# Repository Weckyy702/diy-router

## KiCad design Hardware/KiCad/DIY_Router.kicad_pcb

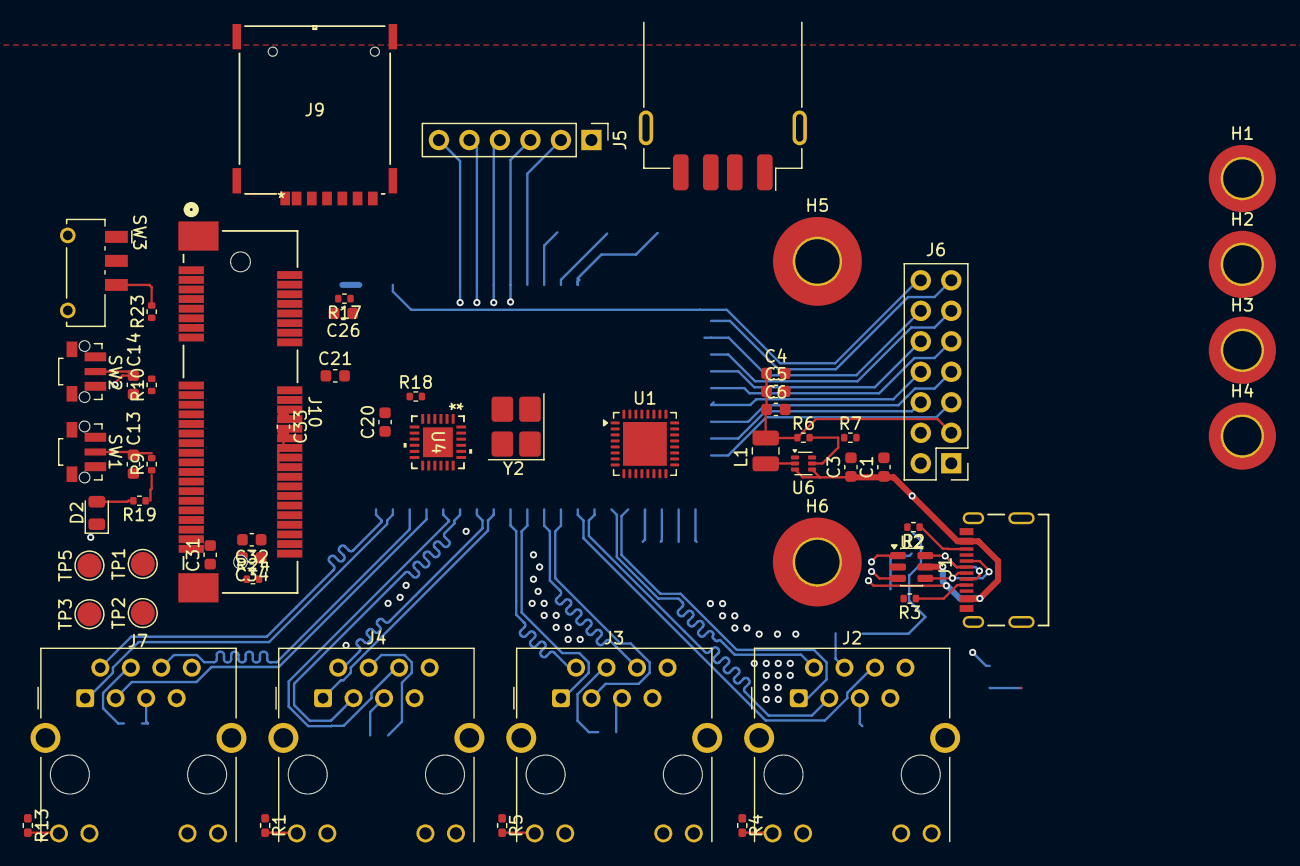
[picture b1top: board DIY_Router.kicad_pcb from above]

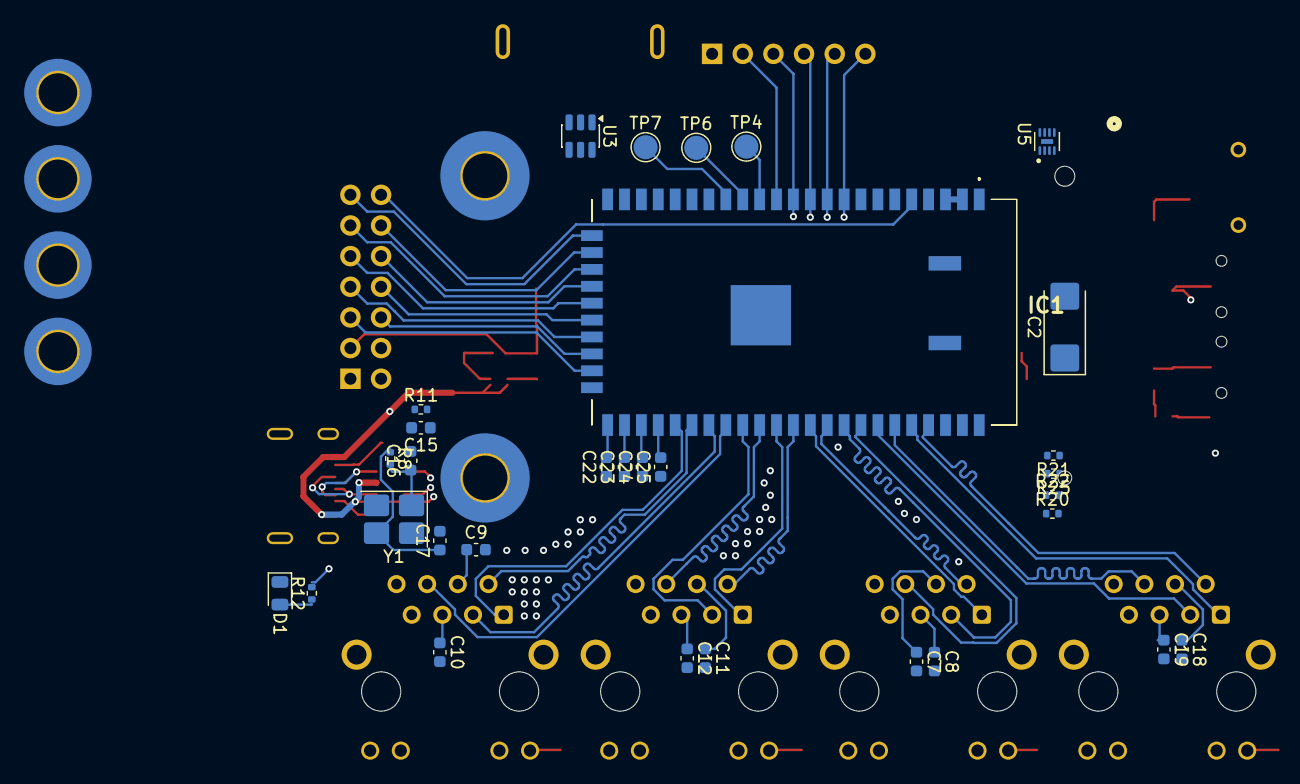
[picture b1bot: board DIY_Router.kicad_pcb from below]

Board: 4 copper layers, 90 parts (31 on the bottom side), 101 nets.

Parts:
C1, C3, C4, C5, C6: 22μF; C_0603_1608Metric
C2: 470µF; CP_EIA-6032-28_Kemet-C_HandSolder
C7, C8, C9, C10, C11, C12, C13, C14, C18, C19, C22, C23, C24, C25, C26, C31, C33: 100nF; C_0603_1608Metric
C15: 4.7µF; C_0603_1608Metric
C16, C17, C20, C21: 18pF; C_0603_1608Metric
C32: 1pF; C_0603_1608Metric
C34: 1µF; C_0603_1608Metric
D1, D2: LED; LED_0805_2012Metric
H1, H2, H3, H4: MountingHole_Pad; MountingHole_3.2mm_M3_DIN965_Pad_TopBottom
H5, H6: MountingHole_Pad; MountingHole_3.7mm_Pad_TopBottom
IC1: HLK-7628N; HLK7628N
J1: 2171790001; MOLEX_2171790001
J2, J3, J4, J7: RJ45_Hanrun_HR911105A_Horizontal
J5: Conn_01x06_Pin; PinHeader_1x06_P2.54mm_Vertical
J6: Conn_02x07_Odd_Even; PinHeader_2x07_P2.54mm_Vertical
J8: USB_A; USB_A_Receptacle_GCT_USB1046
J9: SIM8066-6-1-14-01-A; CONN_SIM8066-6-1-14-01-A_GCT
J10: 2041262-1; CONN60_2041262-1_TEC
L1: MGV252010R22M-10; L_1008_2520Metric
R1, R4, R5, R13: 1kR; R_0402_1005Metric_Pad0.72x0.64mm_HandSolder
R2, R3: 5.1kR; R_0402_1005Metric
R6: 453kR; R_0402_1005Metric
R7, R24, R25: 100kR; R_0402_1005Metric
R8: 1MR; R_0402_1005Metric
R9, R10, R23: 10kR; R_0402_1005Metric
R11: 226R 1%; R_0402_1005Metric
R12, R19: 220R; R_0402_1005Metric
R17: 15kR; R_0402_1005Metric
R18: 12kR 1%; R_0402_1005Metric
R20, R21, R22: 50kR; R_0402_1005Metric
SW1, SW2: 436333033816; SW_Wurth_WS-TASU_436333033816
SW3: 450405020524; SW_Wurth_WS-SLSU_450405020524
TP1, TP2, TP3, TP4, TP5, TP6, TP7: TestPoint; TestPoint_Pad_D2.0mm
U1: XR22801IL32TR-F; QFN-32-1EP_5x5mm_P0.5mm_EP3.65x3.65mm
U2, U3: USBLC6-2SC6Y; SOT-23-6
U4: USB2422T/MJ; SQFN24_4X4MC_MCH
U5: EMIF03-SIM02M8; SON40P170X150X60-9N
U6: TPS62A06ADRLR; SOT-563
Y1: ABM8-25.000MHZ-B2-T3; Crystal_SMD_3225-4Pin_3.2x2.5mm_HandSoldering
Y2: ABM8-24.000MHZ-B2-T; Crystal_SMD_3225-4Pin_3.2x2.5mm_HandSoldering

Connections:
+3.3V: C2.1, C4.1, C5.1, C6.1, C31.2, C33.1, C34.1, IC1.2 (3.3VD_1), IC1.3 (3.3VD_2), J6.3, J10.2, J10.39, J10.41, J10.52, L1.2, R1.1, R4.1, R5.1, R6.1, R9.1, R10.1, R13.1, R19.1, R21.2, U4.18 (VDD33)
/DIY_Router/GPIO0: IC1.30 (GPIO0), J6.7
/DIY_Router/I2C_SCL: IC1.24 (I2C_SCLK), J6.13
/DIY_Router/I2C_SDA: IC1.25 (I2C_SD), J6.12
/DIY_Router/SPI_CLK: IC1.27 (SPI_CLK), J6.10
/DIY_Router/SPI_CS0: IC1.5 (SPI_CS0), J6.14
/DIY_Router/SPI_CS1: IC1.26 (SPI_CS1), J6.11
/DIY_Router/SPI_MISO: IC1.28 (SPI_MISO), J6.9
/DIY_Router/SPI_MOSI: IC1.29 (SPI_MOSI), J6.8
/Mini_PCIe_SIM/LED_WWAN: D2.1 (K), J10.42
/Mini_PCIe_SIM/USIM_CLK: J10.12, U5.3 (CLKIN)
/Mini_PCIe_SIM/USIM_DATA: J10.10, U5.4 (DATAIN)
/Mini_PCIe_SIM/USIM_RST: J10.14, U5.2 (RSTIN)
/Mini_PCIe_SIM/W_DISABLE: J10.20, R23.1, TP2.1 (1_1)
/USB_Ethernet_UART_Bridge/CAP: C15.1, U1.3 (CAP1), U1.20 (CAP2)
/USB_Ethernet_UART_Bridge/XTALIN: C17.1, R8.1, U1.10 (XTALIN), Y1.3
/USB_Ethernet_UART_Bridge/XTALOUT: C16.1, R8.2, U1.9 (XTALOUT), Y1.1
/USB_HUB/USB_OUT_DN: U3.4 (I/O2), U4.2 (USBDM_DN1*PART_DIS_M1)
/USB_HUB/USB_OUT_DP: U3.6 (I/O1), U4.3 (USBDP_DN1*PART_DIS_P1)
/USB_HUB/XTALIN: C21.1, U4.22 (XTALIN*CLKIN), Y2.3
/USB_HUB/XTALOUT: C20.1, U4.21 (XTAOUT*(CLKIN_EM)), Y2.1
CPU_RST: C13.1, IC1.14 (PORST_N), R9.2, SW1.2, TP4.1 (1_1)
EPHY_LED0: IC1.13 (EPHY_LED0), J5.2
EPHY_LED1: IC1.12 (EPHY_LED1), J2.10, J5.3
EPHY_LED2: IC1.11 (EPHY_LED2), J3.10, J5.4
EPHY_LED3: IC1.10 (EPHY_LED3), J4.10, J5.5
EPHY_LED4: IC1.9 (EPHY_LED4), J5.6, J7.10
ETH_RX+: C24.1, U1.15 (ETH_RX+)
ETH_RX-: C25.1, U1.16 (ETH_RX-)
ETH_TX+: C22.1, U1.14 (ETH_TX+)
ETH_TX-: C23.1, U1.13 (ETH_TX-)
GND: C1.2, C2.2, C3.2, C4.2, C5.2, C6.2, C7.2, C8.2, C9.2, C10.2, C11.2, C12.2, C13.2, C14.2, C15.2, C16.2, C17.2, C18.2, C19.2, C20.2, C21.2, C26.1, C31.1, C32.1, D1.1 (K), H1.1 (1_1), H2.1 (1_1), H3.1 (1_1), H4.1 (1_1), H5.1 (1_1), H6.1 (1_1), IC1.1 (GND_1), IC1.4 (GND_2), IC1.21 (GND_3), IC1.23 (GND_4), IC1.56 (GND_5), IC1.EP1, IC1.EP2, IC1.EP3, J1.A1B12 (GND1), J1.B1A12 (GND2), J1.SH1 (SHIELD1), J1.SH2 (SHIELD2), J1.SH3 (SHIELD3), J1.SH4 (SHIELD4), J2.8, J2.SH, J3.8, J3.SH, J4.8, J4.SH, J5.1, J6.1, J6.2, J7.8, J7.SH, J8.4 (GND), J8.SH (Shield), J9.C5 (GND), J9.GND1, J9.GND2, J9.GND3, J9.GND4, J10.4, J10.9, J10.15, J10.18, J10.21, J10.26, J10.27, J10.29, J10.34, J10.35, J10.37, J10.40, J10.43, J10.50, R2.2, R3.2, R7.2, R11.1, R18.2, R20.2, R22.2, R25.1, SW1.1 (A), SW1.3, SW2.1 (A), SW2.3, SW3.2, U1.4 (GND), U1.12 (GND), U1.21 (GND), U1.22 (GND), U1.28 (GND), U1.33 (EPAD), U2.2 (GND), U3.2 (GND), U4.25 (EPAD), U5.9 (GND), U6.1 (GND), Y1.2 (G), Y1.4 (G), Y2.2 (G), Y2.4 (G)
MDI_P0_RN: C23.2, IC1.35 (MDI_RN_P0)
MDI_P0_RP: C22.2, IC1.34 (MDI_RP_P0)
MDI_P0_TN: C25.2, IC1.37 (MDI_TN_P0)
MDI_P0_TP: C24.2, IC1.36 (MDI_TP_P0)
MDI_P1_RN: IC1.41 (MDI_RN_P1), J2.6 (RD-)
MDI_P1_RP: IC1.40 (MDI_RP_P1), J2.3 (RD+)
MDI_P1_TN: IC1.39 (MDI_TN_P1), J2.2 (TD-)
MDI_P1_TP: IC1.38 (MDI_TP_P1), J2.1 (TD+)
MDI_P2_RN: IC1.43 (MDI_RN_P2), J3.6 (RD-)
MDI_P2_RP: IC1.42 (MDI_RP_P2), J3.3 (RD+)
MDI_P2_TN: IC1.45 (MDI_TN_P2), J3.2 (TD-)
MDI_P2_TP: IC1.44 (MDI_TP_P2), J3.1 (TD+)
MDI_P3_RN: IC1.49 (MDI_RN_P3), J4.6 (RD-)
MDI_P3_RP: IC1.48 (MDI_RP_P3), J4.3 (RD+)
MDI_P3_TN: IC1.47 (MDI_TN_P3), J4.2 (TD-)
MDI_P3_TP: IC1.46 (MDI_TP_P3), J4.1 (TD+)
MDI_P4_RN: IC1.51 (MDI_RN_P4), J7.6 (RD-)
MDI_P4_RP: IC1.50 (MDI_RP_P4), J7.3 (RD+)
MDI_P4_TN: IC1.53 (MDI_TN_P4), J7.2 (TD-)
MDI_P4_TP: IC1.52 (MDI_TP_P4), J7.1 (TD+)
unnamed: C33.2, U4.1 (VDD33)
unnamed: C34.2, U4.9 (VDD33)
unnamed: D1.2 (A), R12.1
unnamed: D2.2 (A), R19.2
unnamed: J1.A5 (CC1), R3.1
unnamed: J1.B5 (CC2), R2.1
unnamed: J2.9, R4.2
unnamed: C10.1, J2.5 (RCT)
unnamed: C9.1, J2.4 (TCT)
unnamed: J3.9, R5.2
unnamed: C12.1, J3.5 (RCT)
unnamed: C11.1, J3.4 (TCT)
unnamed: J4.9, R1.2
unnamed: C8.1, J4.5 (RCT)
unnamed: C7.1, J4.4 (TCT)
unnamed: J7.9, R13.2
unnamed: C19.1, J7.5 (RCT)
unnamed: C18.1, J7.4 (TCT)
unnamed: J8.3 (D+), U3.1 (I/O1)
unnamed: J8.2 (D-), U3.3 (I/O2)
unnamed: J9.C3 (CLK), U5.6 (CLKEXT)
unnamed: J9.C7 (I/O), R17.1, U5.5 (DATAEXT)
unnamed: J9.C2 (RST), U5.7 (RSTEXT)
unnamed: R23.2, SW3.3
unnamed: R12.2, U1.19 (ETH_LINK)
unnamed: R11.2, U1.2 (REXT)
unnamed: C32.2, U4.10 (CRFILT)
unnamed: R18.1, U4.24 (RBIAS)
unnamed: TP1.1 (1_1), U4.15 (RESET_N)
unnamed: R20.1, U4.14 (SMBCLK*CFG_SEL0)
unnamed: R21.1, U4.13 (SMBDATA*NON_REM1)
unnamed: R22.1, U4.17 (SUSP_IND*LOCAL_PWR*(NON_REM0))
unnamed: R24.1, R25.2, U4.16 (VBUS_DET)
unnamed: R6.2, R7.1, U6.5 (FB)
unnamed: L1.1, U6.2 (SW)
SLEEP_DTR: J10.31, TP3.1 (1_1)
SOM_USB_DN: IC1.55 (USB_DM), U4.19 (USBDM_UP)
SOM_USB_DP: IC1.54 (USB_DP), U4.20 (USBDP_UP)
UART_RXD0: IC1.32 (UART_RXD0), J6.5, U1.24 (E7/TX)
UART_RXD1: IC1.16 (UART_RXD1), J10.13, TP7.1 (1_1)
UART_TXD0: IC1.31 (UART_TXD0), J6.6, U1.23 (E6/RX/*RWK)
UART_TXD1: IC1.15 (UART_TXD1), J10.11, TP6.1 (1_1)
USB_C_DN: J1.A7 (DN1), J1.B7 (DN2), U1.5 (USBD-), U2.1 (I/O1), U2.6 (I/O1)
USB_C_DP: J1.A6 (DP1), J1.B6 (DP2), U1.6 (USBD+), U2.3 (I/O2), U2.4 (I/O2)
USB_WWAN_DN: J10.36, U4.4 (USBDM_DN1*PART_DIS_M2)
USB_WWAN_DP: J10.38, U4.5 (USBDP_DN1*PART_DIS_P2)
VBUS: C1.1, C3.1, J1.A4B9 (VBUS1), J1.B4A9 (VBUS2), J6.4, J8.1 (VBUS), R24.2, U1.7 (VCC), U2.5 (VBUS), U3.5 (VBUS), U6.3 (VIN), U6.4 (EN)
VCC: C26.2, J9.C1 (VCC), J10.8, R17.2, U5.1 (VCC), U5.8 (VCC)
WDT_RST: C14.1, IC1.8 (WDT_RST_N), R10.2, SW2.2, TP5.1 (1_1)

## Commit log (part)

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2026-06-11 Add KiCad project files, Doc and Software and Hardware folders - KiCad Project contains: o Footprints for: - HLK-7628N - Molxex USB-C 2171790001 o Changes: - Add HLK-7628N module - Add 3.3V power sup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
2026-06-11 Doc: Add datasheets and app notes for important chips
2026-06-11 Add datasheet for MT7628 SOC Add footprints and symbol for Max Linear XR22801 USB Ethernet UART bridge Add sheet for XR22801 Add GPIO and JTAG headers in main sheet
2026-06-12 Add USB ESD protection USBLC6-2SC6Y Edit GPIO pin header
2026-06-12 Remove lock files
2026-06-16 Add dev-shell flake
2026-06-16 Add Quectel EC25 Mini PCIe datasheet
2026-06-16 USB_Bridge: add transformerless connection between usb bridge and SOM
    - Ethernet: Add fourth rj45 jack
2026-06-18 Add Mini PCIe slot TE 2041626 Add Mini PCIe mounting holes and board mounting holes Add nano SIM card slot SIM8066 Add SIM ESD and EMI filter EMIF03-SIM02M8 Add USB Hub USB2422 Add USB A port with ES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
2026-06-23 Add switches for cpu reset and watchdog reset Add swtich for WWAN wirless disable Fix USB2422 VBUS-DET and NON_REM strap pins
2026-06-23 Fix footprints for Mini PCIe and switches (set pads for mounting and case to GND) Set PCB to 4 layer with 0.5 OZ (0,017mm) copper on the inner layers Start sorting the footprints on the PCB TO-DO: ch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
